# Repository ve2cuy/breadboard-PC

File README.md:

# breadboard-PC — an 8088 computer on a breadboard

A microcomputer with a PC/XT-inspired architecture, built on solderless breadboards around an
**Intel 8088**. Its ROM, whose source code is **written entirely in 8086 assembly language**, boots
into an interactive menu, runs two BASIC interpreters and **boots PC-DOS 2.1, MS-DOS 3.30, 5.0 and
6.22** from 160 KB to 1.44 MB floppy disk images.

A project by Alain Boudreault (VE2CUY), 2026. *[Version française](README_fr.md)*

<p align="center">
  <br>
  <em>The build: the Black Pill STM32F411 bridge (top centre), the 8088, the 8255, the 8259, the ROM and
  the RAM. The LCD shows the “Information” screen (date and time, versions, RAM, disk, speed).</em>
</p>

## At a glance

| | |
|---|---|
| **Processor** | Intel 8088, 4.77 MHz by default, adjustable from 1 to 10 MHz (tested up to 7.38 MHz) |
| **Memory** | 256 KB ROM (W29C020C, `C0000h`–`FFFFFh`); **512 KB** static RAM (AS6C4008, `00000h`–`7FFFFh`), 510 KB of it for DOS |
| **I/O** | 8255A in mode 2 (bus to the bridge), 8259A (interrupts), 4×20 I2C LCD, PS/2 keyboard |
| **Bridge** | WeAct **Black Pill STM32F411** board (firmware 1.6): keyboard, USB terminal, LCD, clock, disk, RESET |
| **Software** | ROM written entirely in assembly (NASM, strict 8086 instruction set): menu, BIOS for DOS, Tiny BASIC, GW-BASIC-style BASIC, RAM test with a memory map |
| **Operating systems** | PC-DOS 2.1, MS-DOS 3.30, 5.0 and 6.22, booted from a floppy disk image (160 KB to 1.44 MB) |

## The build

The core of the machine (processor, address latches, data buffer, ROM, RAM, decoding) is wired on
breadboards with 74LS/74HC logic and no programmable logic (no GAL, no CPLD):

- two **74LS373** latch `A0`–`A7` and `A16`–`A19` on `ALE`; a **74HC245** buffers `D0`–`D7`
  (`DEN`, `DT/R`);
- two **74LS00** do all the decoding, with `M` = memory cycle (`IO/M` = 0):
  - **ROM**: `CE# = NAND(A19, M)` — `C0000h`–`FFFFFh`;
  - **RAM**: `CE# = NAND(/A19, M)` — `00000h`–`7FFFFh`;
  - **8255** (ports `80h`–`83h`): `CS# = NAND(IO, A7)`;
  - **8259** (ports `20h`–`21h`): `CS# = NAND(IO, A5)`;
- the 8088's `RD#` and `WR#` go straight to the ROM, the RAM, the 8255 and the 8259.

<p align="center">
  <br>
  <em>Schematic of the build (KiCad, <a href="kicad/Breadboard-pc">kicad/Breadboard-pc</a>). The clock comes from the
  bridge (<code>CLK_STM</code>) or from an external input, selected by jumper JP1. On the PCB, a third 74LS373 (U12)
  also latches A8-A11, so the whole address bus (A0-A19) can drive two 10-LED bargraphs (readable when single-stepping or halted); J5 brings the bus
  out on a 2 x 20 header.</em>
</p>

<p align="center">
  <br>
  <em>PCB v2 (120 x 124.2 mm, 2 layers), KiCad 3D render: 8088, ZIF socket for the ROM, Black Pill bridge (U5),
  512 KB RAM, 8255, 8259, address bargraphs and J5 bus connector. Routed with Freerouting.</em>
</p>

### The signals in action

The animation follows the machine from RESET to DOS reading a sector: the reset vector fetched from
ROM, a RAM write, programming the 8259 and the interrupt vector table (IVT), a key press and the `IRQ1`
interrupt, a BIOS call (`INT 13h`) and the bridge's burst reply. For each step: the chips involved, the
level of the control signals and the memory area targeted.

The animation is generated by [medias/animation/generer_signaux.py](medias/animation/generer_signaux.py).

## The circuit

The 8088 does not bit-bang any peripheral. All traffic goes through **a single 8255 in mode 2**: an
8-bit bidirectional bus with hardware handshaking, connected to the bridge. Every byte received from
the bridge raises an interrupt (`IR1` of the 8259); during a bridge command, `IR1` is masked and the
BIOS polls for the replies.

```mermaid
flowchart LR
    CPU["Intel 8088"] --- BUS(("Bus<br>A0-A19 / D0-D7"))
    BUS --- ROM["256 KB ROM<br>W29C020C"]
    BUS --- RAM["512 KB RAM<br>AS6C4008"]
    BUS --- PIO["8255A<br>mode 2"]
    BUS --- PIC["8259A"]
    PIO -- "INTR → IR1" --> PIC
    PIC -- INTR --> CPU
    PIO <== "Port A (8 bits) + handshake" ==> BRIDGE["Bridge<br>Black Pill STM32F411"]
    BRIDGE -- "CLK, RESET" --> CPU
    KBD["PS/2 keyboard"] --> BRIDGE
    BRIDGE <-- "USB (serial + drive)" --> PC["PC: terminal"]
    BRIDGE --> LCD["4×20 I2C LCD"]
    BRIDGE --- FLASH["8 MB flash<br>FAT16"]
```

The bridge wiring in detail (pins, 3.3 V / 5 V levels, pull-up resistors) is described (in French) in
[arduino/8088_bridge_stm32/README.md](arduino/8088_bridge_stm32/README.md).

## The STM32 bridge

The bridge firmware (a PlatformIO project, [arduino/8088_bridge_stm32](arduino/8088_bridge_stm32))
gives the 8088 the peripherals of a PC:

| Function | Details |
|---|---|
| **PS/2 keyboard** | Frame decoding; raw scan codes passed to the 8088 |
| **Terminal** | Native USB serial port to the PC (ANSI, 80 columns, UTF-8) |
| **Display** | 4×20 HD44780 LCD over I2C (PCF8574) |
| **Real-time clock** | STM32 RTC (32.768 kHz crystal): `TIME$`, `DATE$`, `INT 1Ah` |
| **Disk** | 8 MB W25Q64 SPI flash formatted FAT16: files, sectors, floppy images mounted as A: (read-only ones too) |
| **Throughput** | Replies sent **in bursts**, as soon as the 8088 has read the previous byte (firmware 1.6) |
| **USB drive** | The flash is exposed to the PC as a USB drive (`USB ON` / `USB OFF`) to copy files onto it |
| **8088 clock** | `CLK` signal generated by hardware PWM, 1 to 10 MHz |
| **8088 RESET** | Held while the bridge starts up; **Ctrl-Alt-Del** (PS/2) or **Ctrl-\\** (terminal) |

The 8088 talks to the bridge through a command protocol on a dedicated channel
(see [Solution-01/lib/bridge.asm](Solution-01/lib/bridge.asm)). The firmware is flashed over USB, with
the board in DFU mode: `platformio run -e blackpill_f411ce_usbdrive -t upload`.

## The menu

At power-up, the ROM displays a menu on both the terminal and the LCD. It can be driven from either
the PS/2 keyboard or the terminal; **Esc** goes back to the previous menu.

| Menu | Options |
|---|---|
| **1) Basic** | Tiny BASIC; GW-BASIC-style BASIC |
| **2) Memory functions** | Memory dump and editing, CPU registers, code entry and execution, interrupt vector table; **RAM test**: *Trace* (full progress), *MAP* (memory map and summary only) or *Loop* (MAP repeated until Esc) |
| **3) USB Disk** | USB drive toggle, file list, **booting a disk image** |
| **4) Configuration** | Clock speed (0.1 and 1 MHz steps; 2.35, 4.77, 8 and 7.2 MHz presets), CPU speed test, date and time, information screen |

The **RAM test** checks all 512 KB byte by byte (the test stack is moved to low RAM, the last 2 KB are
tested separately), then the address lines `A0`–`A18` (the chip's real capacity). It ends with a
**memory map** (one character per KB) and the good and faulty amounts.

## BASIC

An original reimplementation inspired by GW-BASIC: same keywords, same error messages, integers,
single-precision floating point (in software) and strings. About 54 KB are free for programs.

| Category | Commands and functions |
|---|---|
| **Program** | `RUN` `LIST` `EDIT` `DELETE` `NEW` `CLEAR` `CONT` `TRON` `TROFF` `HELP` `SYSTEM` |
| **Control flow** | `IF…THEN…ELSE` `GOTO` `GOSUB`/`RETURN` `ON…GOTO/GOSUB` `FOR…NEXT` `WHILE…WEND` `END` `STOP` |
| **Data** | `LET` `DIM` `ERASE` `SWAP` `DATA`/`READ`/`RESTORE` `DEF FN` `DEFINT`/`DEFSNG`/`DEFSTR` |
| **Input/output** | `PRINT` `INPUT` `LINE INPUT` `INKEY$` `CLS` `LOCATE` `COLOR` `BEEP` |
| **Math** | `ABS` `SGN` `INT` `FIX` `SQR` `SIN` `COS` `TAN` `ATN` `LOG` `EXP` `RND` `RANDOMIZE` |
| **Strings** | `LEN` `LEFT$` `RIGHT$` `MID$` `INSTR` `CHR$` `ASC` `STR$` `VAL` `HEX$` `UCASE$` `STRING$` |
| **Files** | `SAVE` `LOAD` `MERGE` `FILES` `KILL` `FORMAT`; `OPEN` `PRINT #` `INPUT #` `EOF` `CLOSE` |
| **Clock** | `TIMER` `TIME$` `DATE$` (read and set the bridge RTC) |
| **Machine** | `PEEK` `POKE` `DEF SEG` `INP` `OUT` `WAIT` `CALL` `FRE` |
| **Disk and system** | `DSKREAD` `DSKWRITE` `USB ON`/`OFF` `BOOT "image.img"` |

## DOS 2.1 to 6.22

The ROM provides the BIOS layer a DOS expects: disk (`INT 13h`, CHS and LBA), keyboard (`INT 16h`),
clock (`INT 1Ah`), text output to the terminal (`INT 10h`) and bootstrap (`INT 19h`). A floppy image
copied to the flash (through the USB drive) is mounted as drive **A:** and booted from
**USB Disk → 3) Boot disk image**, or with `BOOT "PCDOS2_1.IMG"` from BASIC. DOS writes go to the
image file; a read-only image is mounted anyway, without write access.

<p align="center">
  <br>
  <em>PC-DOS 2.1: booting from the image (one dot per sector read), VER, DIR /W</em>
</p>

<p align="center">
  <br>
  <em>MS-DOS 3.30</em>
</p>

What makes DOS 5.0 and 6.22 possible:

- **512 KB of RAM** (these versions require at least 256 KB);
- the **model byte** `FEh` (PC/XT) at `F000:FFFE`: without it, DOS 5 takes the AT keyboard path
  (ports `60h`/`64h`), which hits the 8259 with this decoding;
- the BIOS tick counter `0040:006C`, kept in step with the bridge clock (there is no timer on this
  build): DOS 6 times its F5/F8 boot pause with it;
- **1.44 MB** floppies (geometry from the image size, `INT 13h AH=08h/18h`).

DOS accented letters and box-drawing characters (code page 437) are converted to **UTF-8** on the
terminal: the PC terminal must be set to UTF-8.

Limitations: no video hardware (programs that write to video memory display nothing); DOS keyboard
input from the terminal only; **KEYB** does not work (it reads the keyboard through port `60h`) —
setup disks that start it from `AUTOEXEC.BAT` must have it removed (see the `-nokeyb` copies in
[PC-DOS/](PC-DOS)).

## Building the ROM

```sh
cd Solution-01
make            # solution-01.bin (256 KB, 512 KB RAM); make rom-en for English; make rom-128: 128 KB RAM
make check      # checks size, reset vector, signature and model byte
make test       # test benches under emulation (Unicorn)
make test-rom   # full ROM simulation: DOS, BASIC, PS/2 keyboard
```

Tools: NASM, GNU Make, Python 3 (+ `unicorn` for the tests); PlatformIO for the bridge.

## Repository layout

| Folder | Contents |
|---|---|
| [Solution-01/](Solution-01) | 8088 ROM (NASM) and tests; full technical documentation (in French) in [Solution-01/README.md](Solution-01/README.md) |
| [arduino/8088_bridge_stm32/](arduino/8088_bridge_stm32) | Firmware of the Black Pill STM32F411 bridge (PlatformIO) |
| [kicad/](kicad) | Schematic and PCB of the build |
| [PC-DOS/](PC-DOS) | Test floppy disk images |
| [medias/](medias) | Datasheets, schematic, PCB render, signal animation and screenshots |

> The terminal screenshots on this page are produced by the actual (English) ROM, running in the
> project's simulator ([medias/captures/generer.py](medias/captures/generer.py)).

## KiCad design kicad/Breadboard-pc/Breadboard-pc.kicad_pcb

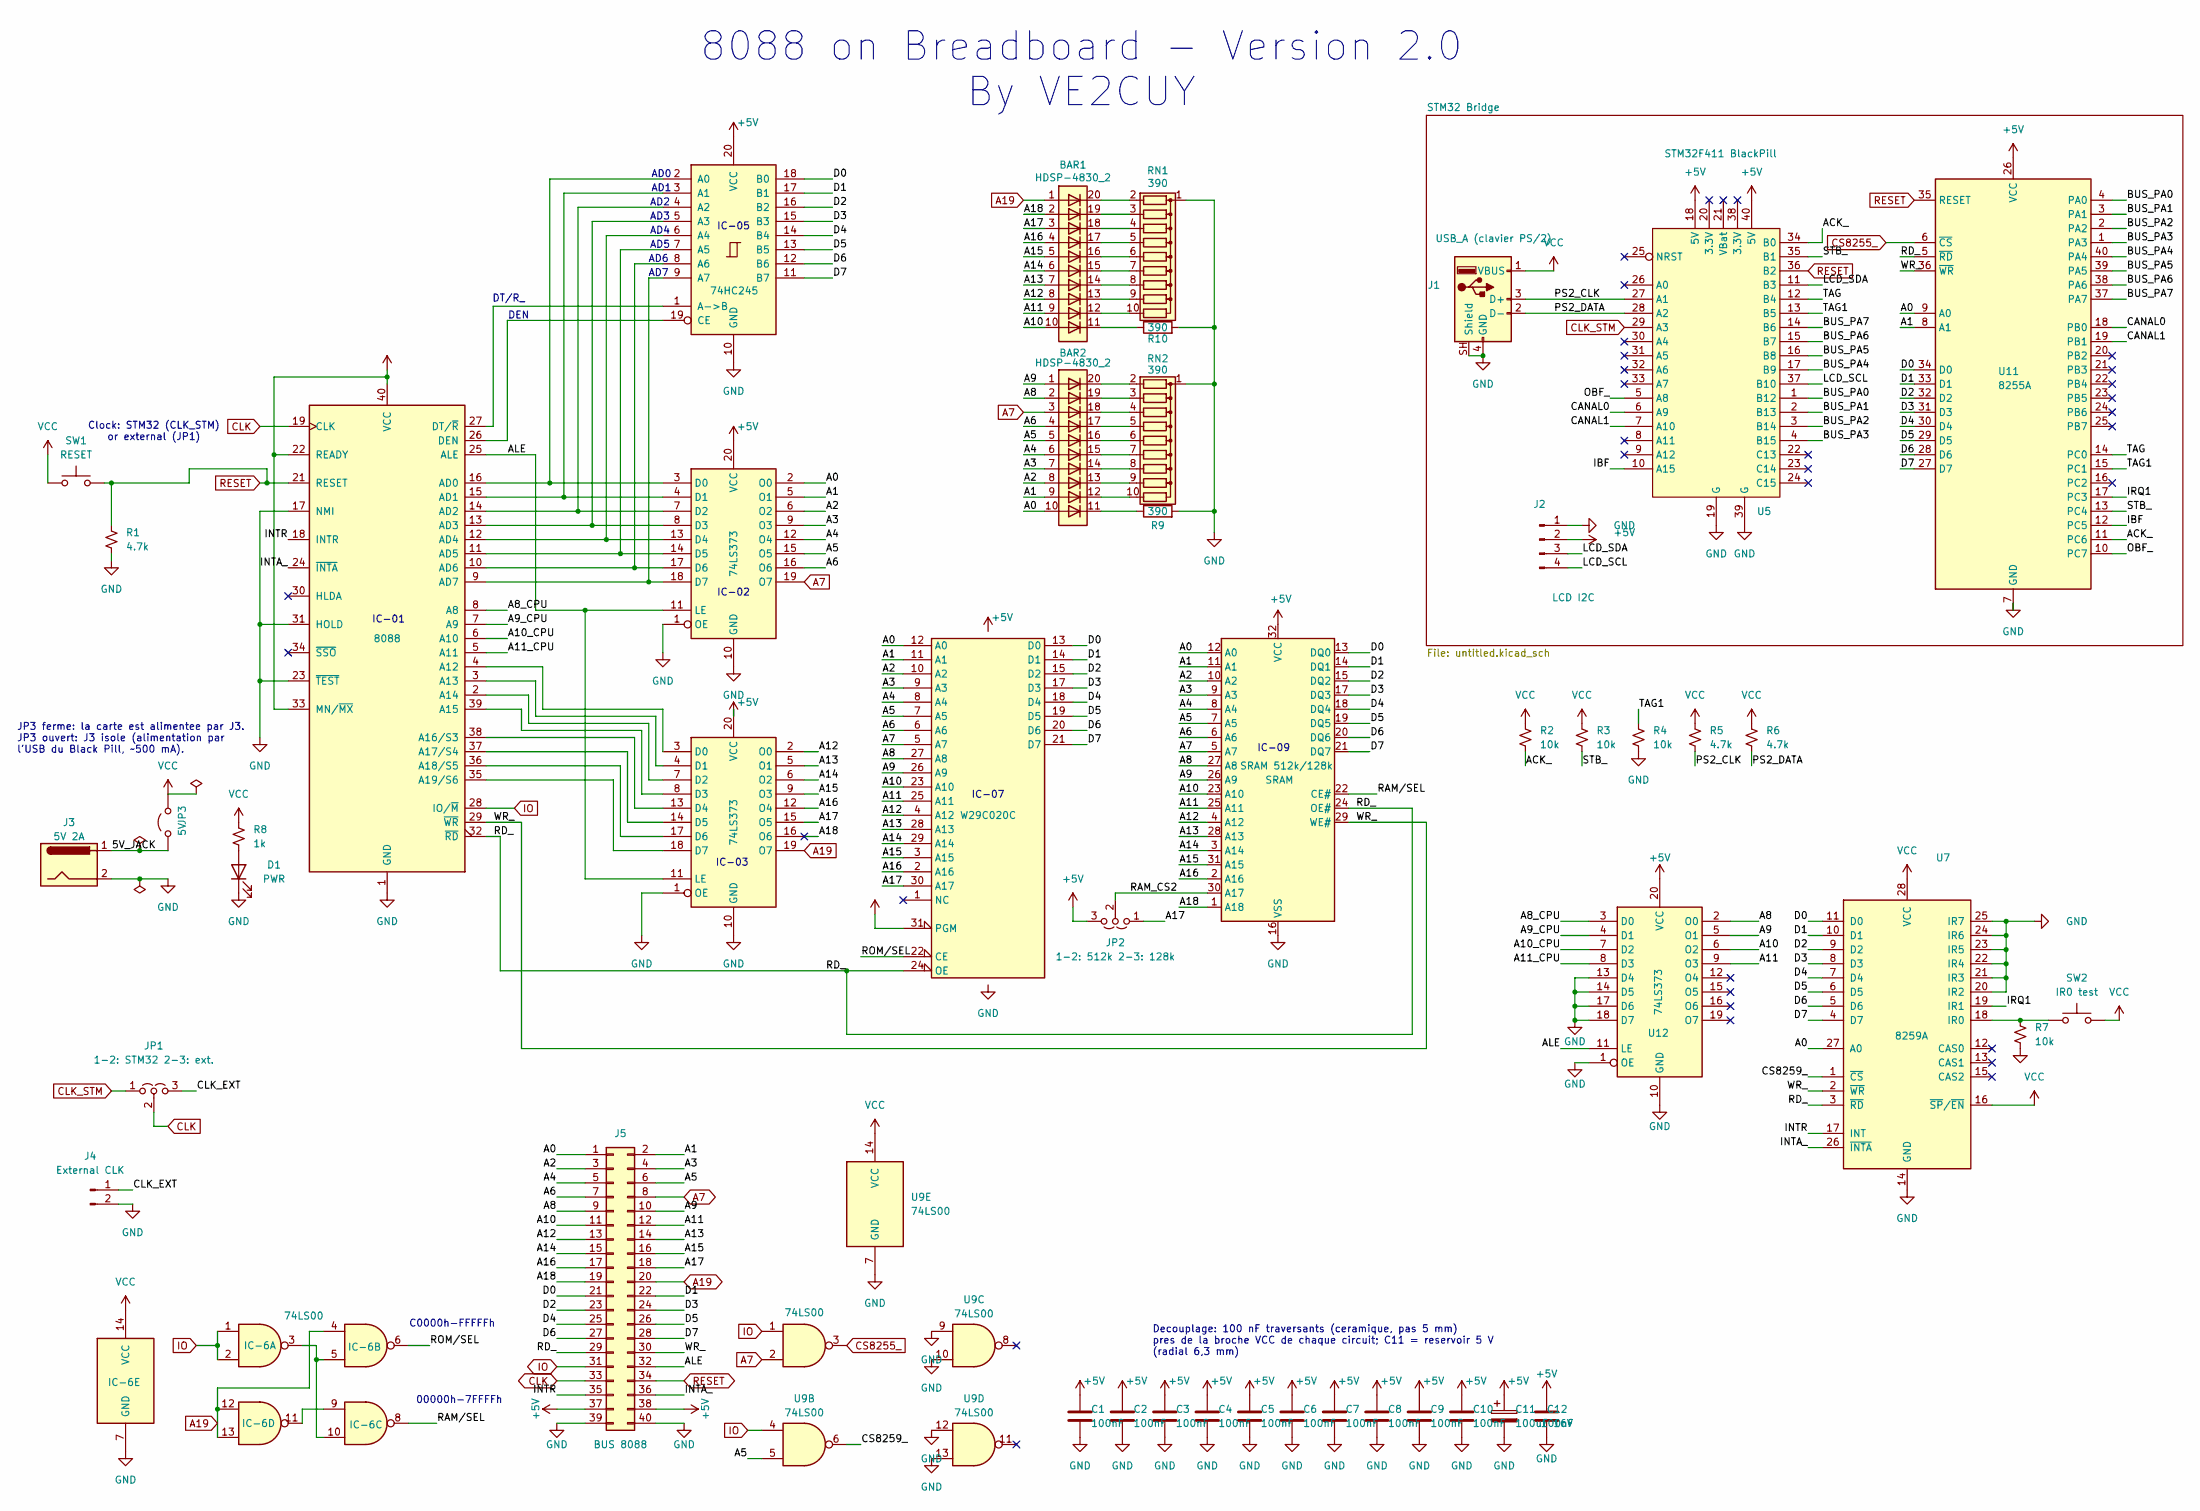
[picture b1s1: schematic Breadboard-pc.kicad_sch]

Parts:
BAR1, BAR2: HDSP-4830_2; HDSP-4830
C1, C2, C3, C4, C5, C6, C7, C8, C9, C10, C12: 100nF; C_Disc_D5.0mm_W2.5mm_P5.00mm
C11: 100uF 16V; CP_Radial_D6.3mm_P2.50mm
D1: PWR; LED_D3.0mm
IC-6: 74LS00; DIP-14_W7.62mm
J1: USB_A (clavier PS/2); USB_A_Molex_67643_Horizontal
J2: LCD I2C; PinHeader_1x04_P2.54mm_Vertical
J3: 5V 2A; BarrelJack_Horizontal
J4: External CLK; PinHeader_1x02_P2.54mm_Vertical
J5: BUS 8088; PinHeader_2x20_P2.54mm_Vertical
JP1: 1-2: STM32 2-3: ext.; PinHeader_1x03_P2.54mm_Vertical
JP2: 1-2: 512k 2-3: 128k; PinHeader_1x03_P2.54mm_Vertical
JP3: 5V; PinHeader_1x02_P2.54mm_Vertical
R1, R5, R6: 4.7k; R_Axial_DIN0207_L6.3mm_D2.5mm_P7.62mm_Horizontal
R2, R3, R4, R7: 10k; R_Axial_DIN0207_L6.3mm_D2.5mm_P7.62mm_Horizontal
R8: 1k; R_Axial_DIN0207_L6.3mm_D2.5mm_P7.62mm_Horizontal
R9, R10: 390; R_Axial_DIN0207_L6.3mm_D2.5mm_P7.62mm_Horizontal
RN1, RN2: 390; R_Array_SIP10
SW1: RESET; SW_PUSH_6mm
SW2: IR0 test; SW_PUSH_6mm
U1: 8088; DIP-40_W15.24mm
U2, U3, U12: 74LS373; DIP-20_W7.62mm
U4: W29C020C; DIP_Socket-32_W11.9mm_W12.7mm_W15.24mm_W17.78mm_W18.5mm_3M_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
U5: STM32F411 BlackPill; STM32F411_Black_Pill
U6: 74HC245; DIP-20_W7.62mm
U7: 8259A; DIP-28_W15.24mm
U8: SRAM; DIP-32_W15.24mm
U9: 74LS00; DIP-14_W7.62mm
U11: 8255A; DIP-40_W15.24mm

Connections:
/5V_JACK: J3.1, JP3.1 (A)
/A0: BAR2.10 (A), J5.1, U2.2 (O0), U4.12 (A0), U7.27 (A0), U8.12 (A0), U11.9 (A0)
/A1: BAR2.9 (A), J5.2, U2.5 (O1), U4.11 (A1), U8.11 (A1), U11.8 (A1)
/A2: BAR2.8 (A), J5.3, U2.6 (O2), U4.10 (A2), U8.10 (A2)
/A3: BAR2.7 (A), J5.4, U2.9 (O3), U4.9 (A3), U8.9 (A3)
/A4: BAR2.6 (A), J5.5, U2.12 (O4), U4.8 (A4), U8.8 (A4)
/A5: BAR2.5 (A), J5.6, U2.15 (O5), U4.7 (A5), U8.7 (A5), U9.5
/A6: BAR2.4 (A), J5.7, U2.16 (O6), U4.6 (A6), U8.6 (A6)
/A8: BAR2.2 (A), J5.9, U4.27 (A8), U8.27 (A8), U12.2 (O0)
/A8_CPU: U1.8 (A8), U12.3 (D0)
/A9: BAR2.1 (A), J5.10, U4.26 (A9), U8.26 (A9), U12.5 (O1)
/A9_CPU: U1.7 (A9), U12.4 (D1)
/A10: BAR1.10 (A), J5.11, U4.23 (A10), U8.23 (A10), U12.6 (O2)
/A10_CPU: U1.6 (A10), U12.7 (D2)
/A11: BAR1.9 (A), J5.12, U4.25 (A11), U8.25 (A11), U12.9 (O3)
/A11_CPU: U1.5 (A11), U12.8 (D3)
/A12: BAR1.8 (A), J5.13, U3.2 (O0), U4.4 (A12), U8.4 (A12)
/A13: BAR1.7 (A), J5.14, U3.5 (O1), U4.28 (A13), U8.28 (A13)
/A14: BAR1.6 (A), J5.15, U3.6 (O2), U4.29 (A14), U8.3 (A14)
/A15: BAR1.5 (A), J5.16, U3.9 (O3), U4.3 (A15), U8.31 (A15)
/A16: BAR1.4 (A), J5.17, U3.12 (O4), U4.2 (A16), U8.2 (A16)
/A17: BAR1.3 (A), J5.18, JP2.1 (A), U3.15 (O5), U4.30 (A17)
/A18: BAR1.2 (A), J5.19, U3.16 (O6), U8.1 (NC)
/ACK_: R2.2, U5.34 (B0), U11.11 (PC6)
/ALE: J5.32, U1.25 (ALE), U2.11 (LE), U3.11 (LE), U12.11 (LE)
/BUS_PA0: U5.1 (B12), U11.4 (PA0)
/BUS_PA1: U5.2 (B13), U11.3 (PA1)
/BUS_PA2: U5.3 (B14), U11.2 (PA2)
/BUS_PA3: U5.4 (B15), U11.1 (PA3)
/BUS_PA4: U5.17 (B9), U11.40 (PA4)
/BUS_PA5: U5.16 (B8), U11.39 (PA5)
/BUS_PA6: U5.15 (B7), U11.38 (PA6)
/BUS_PA7: U5.14 (B6), U11.37 (PA7)
/CANAL0: U5.6 (A9), U11.18 (PB0)
/CANAL1: U5.7 (A10), U11.19 (PB1)
/CLK_EXT: J4.1, JP1.3 (B)
/CS8259_: U7.1 (~CS), U9.6
/D0: J5.21, U4.13 (D0), U6.18 (B0), U7.11 (D0), U8.13 (DQ0), U11.34 (D0)
/D1: J5.22, U4.14 (D1), U6.17 (B1), U7.10 (D1), U8.14 (DQ1), U11.33 (D1)
/D2: J5.23, U4.15 (D2), U6.16 (B2), U7.9 (D2), U8.15 (DQ2), U11.32 (D2)
/D3: J5.24, U4.17 (D3), U6.15 (B3), U7.8 (D3), U8.17 (DQ3), U11.31 (D3)
/D4: J5.25, U4.18 (D4), U6.14 (B4), U7.7 (D4), U8.18 (DQ4), U11.30 (D4)
/D5: J5.26, U4.19 (D5), U6.13 (B5), U7.6 (D5), U8.19 (DQ5), U11.29 (D5)
/D6: J5.27, U4.20 (D6), U6.12 (B6), U7.5 (D6), U8.20 (DQ6), U11.28 (D6)
/D7: J5.28, U4.21 (D7), U6.11 (B7), U7.4 (D7), U8.21 (DQ7), U11.27 (D7)
/IBF: U5.10 (A15), U11.12 (PC5)
/INTA_: J5.36, U1.24 (~INTA), U7.26 (~INTA)
/INTR: J5.35, U1.18 (INTR), U7.17 (INT)
/IRQ1: U7.19 (IR1), U11.17 (PC3)
/LCD_SCL: J2.4, U5.37 (B10)
/LCD_SDA: J2.3, U5.11 (B3)
/OBF_: U5.5 (A8), U11.10 (PC7)
/PS2_CLK: J1.3 (D+), R5.2, U5.27 (A1)
/PS2_DATA: J1.2 (D-), R6.2, U5.28 (A2)
/RAM_CS2: JP2.2 (C), U8.30 (CS2)
/RAM/SEL: IC-6.8, U8.22 (CE#)
/RD_: J5.29, U1.32 (~RD), U4.24 (OE), U7.3 (~RD), U8.24 (OE#), U11.5 (~RD)
/ROM/SEL: IC-6.6, U4.22 (CE)
/STB_: R3.2, U5.35 (B1), U11.13 (PC4)
/TAG: U5.12 (B4), U11.14 (PC0)
/TAG1: R4.1, U5.13 (B5), U11.15 (PC1)
/WR_: J5.30, U1.29 (~WR), U7.2 (~WR), U8.29 (WE#), U11.36 (~WR)
A7: BAR2.3 (A), J5.8, U2.19 (O7), U4.5 (A7), U8.5 (A7), U9.2
A19: BAR1.1 (A), IC-6.4, IC-6.12, IC-6.13, J5.20, U3.19 (O7)
CLK: J5.33, JP1.2 (C), U1.19 (CLK)
CLK_STM: JP1.1 (A), U5.29 (A3)
CS8255_: U9.3, U11.6 (~CS)
GND: C1.2, C2.2, C3.2, C4.2, C5.2, C6.2, C7.2, C8.2, C9.2, C10.2, C11.2, C12.2, D1.1 (K), IC-6.7 (GND), J1.4 (GND), J1.SH (Shield), J2.1, J3.2, J4.2, J5.39, J5.40, R1.2, R4.2, R7.2, R9.2, R10.2, RN1.1 (common), RN2.1 (common), U1.1 (GND), U1.17 (NMI), U1.20 (GND), U1.23 (~TEST), U1.31 (HOLD), U2.1 (OE), U2.10 (GND), U3.1 (OE), U3.10 (GND), U4.16 (GND), U5.19 (G), U5.39 (G), U6.10 (GND), U7.14 (GND), U7.20 (IR2), U7.21 (IR3), U7.22 (IR4), U7.23 (IR5), U7.24 (IR6), U7.25 (IR7), U8.16 (VSS), U9.7 (GND), U9.9, U9.10, U9.12, U9.13, U11.7 (GND), U12.1 (OE), U12.10 (GND), U12.13 (D4), U12.14 (D5), U12.17 (D6), U12.18 (D7)
IO: IC-6.1, IC-6.2, J5.31, U1.28 (IO/~M), U9.1, U9.4
unnamed: BAR1.11 (K), R10.1
unnamed: BAR2.11 (K), R9.1
unnamed: D1.2 (A), R8.2
unnamed: IC-6.3, IC-6.5, IC-6.10
unnamed: IC-6.9, IC-6.11
unnamed: BAR1.20 (K), RN1.2 (R1)
unnamed: BAR1.19 (K), RN1.3 (R2)
unnamed: BAR1.18 (K), RN1.4 (R3)
unnamed: BAR1.17 (K), RN1.5 (R4)
unnamed: BAR1.16 (K), RN1.6 (R5)
unnamed: BAR1.15 (K), RN1.7 (R6)
unnamed: BAR1.14 (K), RN1.8 (R7)
unnamed: BAR1.13 (K), RN1.9 (R8)
unnamed: BAR1.12 (K), RN1.10 (R9)
unnamed: BAR2.20 (K), RN2.2 (R1)
unnamed: BAR2.19 (K), RN2.3 (R2)
unnamed: BAR2.18 (K), RN2.4 (R3)
unnamed: BAR2.17 (K), RN2.5 (R4)
unnamed: BAR2.16 (K), RN2.6 (R5)
unnamed: BAR2.15 (K), RN2.7 (R6)
unnamed: BAR2.14 (K), RN2.8 (R7)
unnamed: BAR2.13 (K), RN2.9 (R8)
unnamed: BAR2.12 (K), RN2.10 (R9)
unnamed: U1.4 (A12), U3.3 (D0)
unnamed: U1.3 (A13), U3.4 (D1)
unnamed: U1.2 (A14), U3.7 (D2)
unnamed: U1.39 (A15), U3.8 (D3)
unnamed: U1.38 (A16/S3), U3.13 (D4)
unnamed: U1.37 (A17/S4), U3.14 (D5)
unnamed: U1.36 (A18/S5), U3.17 (D6)
unnamed: U1.35 (A19/S6), U3.18 (D7)
unnamed: U1.16 (AD0), U2.3 (D0), U6.2 (A0)
unnamed: U1.15 (AD1), U2.4 (D1), U6.3 (A1)
unnamed: U1.14 (AD2), U2.7 (D2), U6.4 (A2)
unnamed: U1.13 (AD3), U2.8 (D3), U6.5 (A3)
unnamed: U1.12 (AD4), U2.13 (D4), U6.6 (A4)
unnamed: U1.11 (AD5), U2.14 (D5), U6.7 (A5)
unnamed: U1.10 (AD6), U2.17 (D6), U6.8 (A6)
unnamed: U1.9 (AD7), U2.18 (D7), U6.9 (A7)
unnamed: U1.26 (DEN), U6.19 (CE)
unnamed: U1.27 (DT/~R), U6.1 (A->B)
unnamed: R7.1, SW2.1, U7.18 (IR0)
RESET: J5.34, R1.1, SW1.2, U1.21 (RESET), U5.36 (B2), U11.35 (RESET)

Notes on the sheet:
IC-07
Decouplage: 100 nF traversants (ceramique, pas 5 mm) pres de la broche VCC de chaque circuit; C11 = reservoir 5 V (radial 6,3 mm)
C0000h-FFFFFh
00000h-7FFFFh
IC-05
AD2
DEN
IC-01
AD5
IC-03
AD4
AD0
DT/R_
IC-09
AD3
JP3 ferme: la carte est alimentee par J3. JP3 ouvert: J3 isole (alimentation par l'USB du Black Pill, ~500 mA).
IC-02
AD6
AD1
Clock: STM32 (CLK_STM) or external (JP1)
AD7
8088 on Breadboard - Version 2.0 By VE2CUY

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
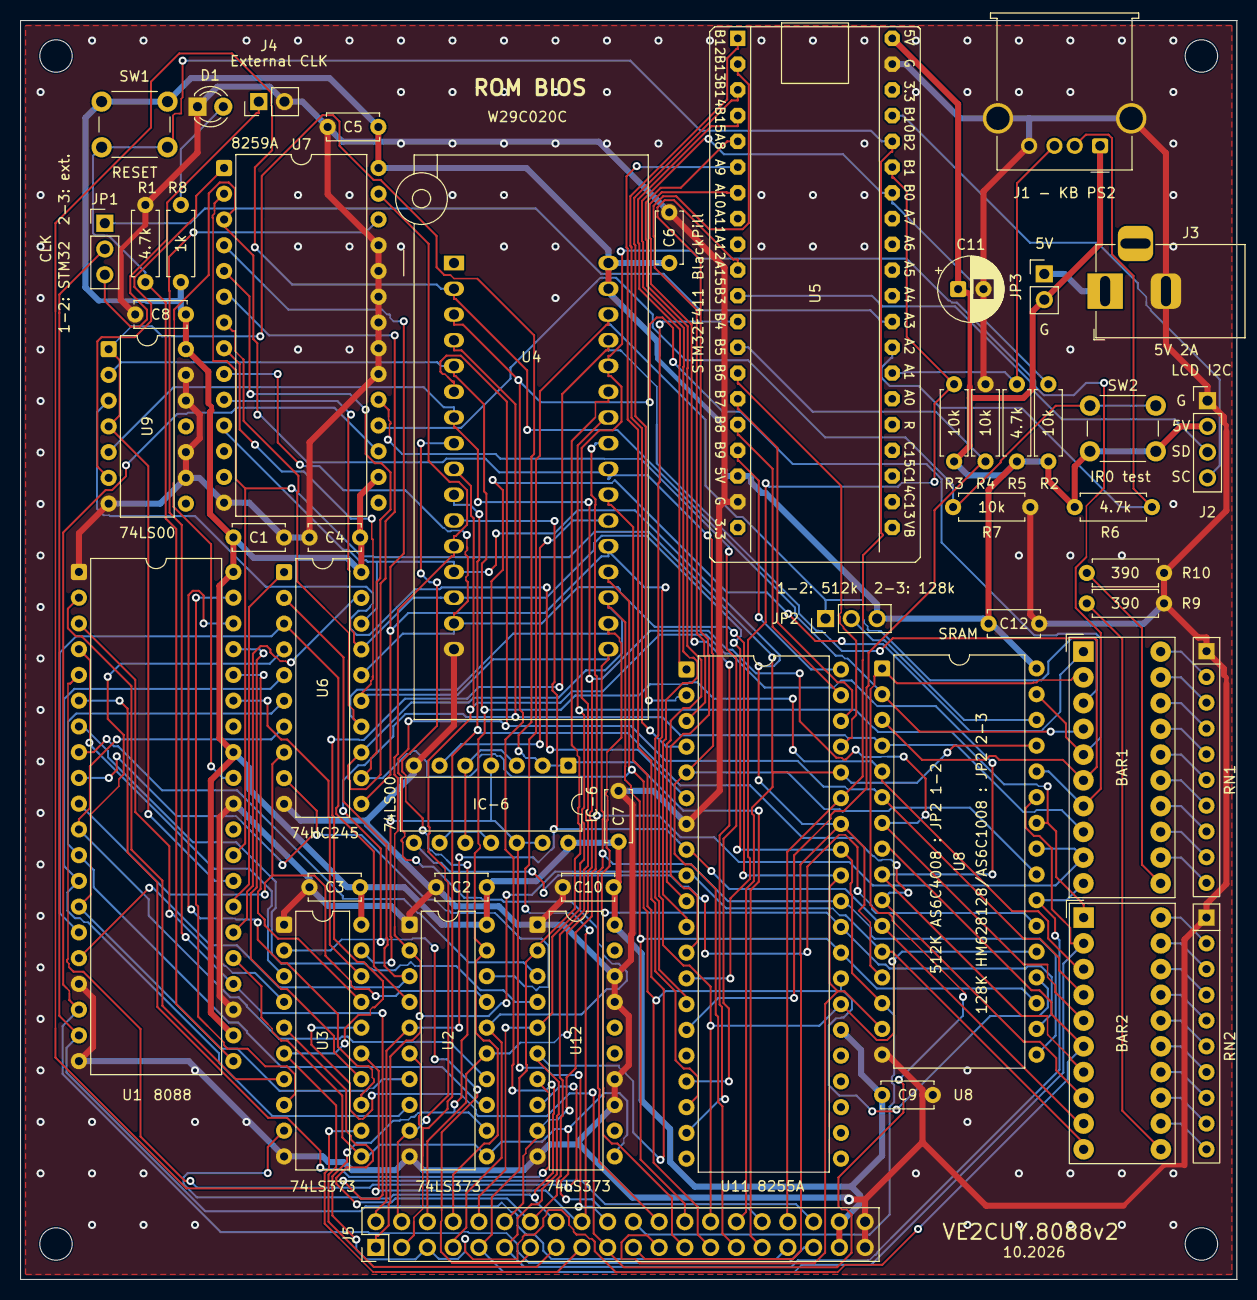
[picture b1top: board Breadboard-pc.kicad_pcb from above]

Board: 2 copper layers, 120.0 x 124.2 mm, 53 parts (0 on the bottom side), 113 nets.

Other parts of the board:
H1, H2, H3, H4: M3; MountingHole_3.2mm_M3

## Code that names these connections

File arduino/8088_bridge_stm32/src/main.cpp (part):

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//   - UART          : port serie virtuel USB (USB natif, "Serial") <-> 8088;
//   - LCD 20x4 I2C  : possede le bus I2C et le protocole PCF8574/HD44780.
//
// 8088 -> pont : le 8088 pose le CANAL sur le Port B (PB0/PB1 du 8255) puis
//     ecrit le Port A; OBF# passe a 0. On lit le canal, on abaisse ACK#, on lit
//     l'octet, on relache ACK#. canal 0 = octet UART, 1 = commande LCD, 2 =
//     donnee LCD.
// pont -> 8088 : on pose l'etiquette TAG (PC0: 0 = scan code, 1 = octet UART
//     recu; PC1 = 1: REPONSE a une commande), l'octet sur le bus, et on pulse
//     STB#; INTR du 8255 (sur IR1 du 8259) interrompt le 8088.
// canal 3 = COMMANDES pour le pont (voir Solution-01/lib/bridge.asm):
//     00h PING (reponse B1h, 3, capacites)   01h LIRE l'heure (reponse: 8 octets)
//     02h + 7 octets REGLER l'heure (annee 2 octets, mois, jour, h, min, s).
//     03h VERSION du firmware (PAS le "3" de PING ci-dessus, qui est le numero
//     de VERSION DU PROTOCOLE - sans rapport) -> 2 octets (majeure, mineure).
//     Necessite TAG1 (PB5) relie a PC1 du 8255 (tire a 0 par 10 kohm).
//     10h-19h = DISQUE: fichiers FAT (racine, noms 8.3) sur la flash SPI (W25Q64, 8 Mo) de la carte
//     (PA4 = CS, SPI1 PA5/PA6/PA7): statut, formater, ouvrir, lire, ecrire, fermer,
//     repertoire (debut / suivant), supprimer, espace libre. Voir lib/bridge.asm.
//     2Ch + 1 octet (action) = HORLOGE du 8088 (PA3, PWM materiel, voir clockExec ci-dessous):
//     0 lire, 1 +0,1 MHz, 2 -0,1 MHz, 3 +1 MHz, 4 -1 MHz, 5 -> 4,77 MHz, 6 -> 8 MHz
//     -> reponse 4 octets = Hz resultant.
//
// CABLAGE (voir le tableau du README.md)
//   D0-D3 <-> PB12-PB15 et D4-D7 <-> PB6-PB9  <->  8255 PA0-PA7 (bus de donnees)
//   PB0 -> ACK# (PC6)   PB1 -> STB# (PC4)   PA8 <- OBF# (PC7)   PB4 -> TAG (PC0)
//   PA9 <- canal bit 0 (8255 PB0)   PA10 <- canal bit 1 (8255 PB1)
//   PA15 <- IBF (PC5, facultatif)   PB5 -> TAG1 (PC1)
//   PA3 -> CLK du 8088 (broche 19, PWM materiel TIM2 CH4 - remplace le fil depuis l'Arduino UNO
//   R4 de projets/Clock-8088/; PA3 servait a TAG2/PC2, jamais cablee sur ce montage - libre)
//   PA1 <- CLK PS/2   PA2 <- DATA PS/2   PB10 = SCL, PB3 = SDA (LCD I2C2)
//   PA11/PA12 = USB, PA13/PA14 = SWD, PC13 = LED, PA4-PA7 = flash SPI (reservees),
//   PB2 -> RESET du 8088 (broche 21, actif HAUT; 4,7 kohm (R1) vers la masse sur le montage, bouton vers +5 V):
//   poussee HAUT pour un reset (demarrage du pont, Ctrl-Alt-Suppr au PS/2, Ctrl-\ au terminal), sinon
//   ENTREE (ne gene pas le bouton, jamais forcee BAS). PB2 = BOOT1: au repos la ligne est BASSE (4,7 kohm),
//   le mode DFU (BOOT0 = 1, BOOT1 = 0) reste donc utilisable.   PA0 = bouton K1 de la carte
// Selon la fiche technique du STM32F411 (DS10314 Rev 8, tableau 8), TOUTES ces
// broches sont tolerantes 5 V (FT) SAUF PA0 et PB5 (TC, 3,3 V): PB5 n'est donc
// utilisee qu'en SORTIE (TAG1). Ne jamais y relier une sortie 5 V.
// ============================================================================
#include <Wire.h>
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
// ---- reglages -------------------------------------------------------------
#define LCD_ADDR    0x27     // 0x3F pour un PCF8574A
// IBF (PC5 du 8255) cable sur PA15 ? 1 = oui: on n'envoie un octet que si le 8088 a lu le
// precedent (aucun octet ecrase); 0 = non cable. Non cable, PA15 est tiree a 0 (= libre).
#define USE_IBF     1
// Espace MINIMAL entre deux octets pont -> 8088, en plus de IBF. Le 8088 met ~ 0,5 ms
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#define IBF_BIT   15                 // GPIOA, entree (facultatif)
#define PS2_CLK_BIT  1               // GPIOA, interruption EXTI1
#define PS2_DATA_BIT 2               // GPIOA
const uint32_t PIN_ACK = PB0, PIN_STB = PB1, PIN_TAG = PB4;
const uint32_t PIN_OBF = PA8, PIN_CH0 = PA9, PIN_CH1 = PA10, PIN_IBF = PA15;
const uint32_t PIN_TAG1 = PB5;                         // PC1 (etiquette etendue, futur)
const uint32_t PIN_PS2_CLK = PA1, PIN_PS2_DATA = PA2;
const uint32_t PIN_SCL = PB10, PIN_SDA = PB3;          // I2C2 (AF4 / AF9)
const uint32_t PIN_CLK8088 = PA3;                      // TIM2 CH4: horloge du 8088 (broche CLK, 19) -
                                                         // remplace le fil depuis l'Arduino UNO R4 (projets/Clock-8088)
                                                         // - PA3 servait a TAG2/PC2, jamais cablee sur ce montage

// Bus de donnees sur GPIOB, en deux quartets: D0-D3 = PB12-PB15, D4-D7 = PB6-PB9
#define BUS_ODR_MASK   ((0xFUL << 12) | (0xFUL << 6))
#define BUS_MODER_MASK 0xFF0FF000UL  // 2 bits par broche: PB12-15 (bits 24-31) et PB6-9 (bits 12-19)
#define BUS_MODER_OUT  0x55055000UL  // 01 = sortie
// Sur le montage, les broches PA4-PA7 du 8255 arrivent dans l'ORDRE INVERSE
// (constate: espace 0x20 recu 0x40, 'p' 0x70 recu 0xE0): le quartet haut est
// inverse (D4<->D7, D5<->D6), comme sur l'UNO. 1 = corrige en logiciel, 0 = bus
// cable dans l'ordre (D0-D7 <-> PA0-PA7).
#define BUS_HIGH_NIBBLE_REVERSED 1

// ---- canaux 8088 -> pont (Port B du 8255) ---------------------------------
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  stbHigh();                               // front montant: le 8255 verrouille
  delayMicroseconds(2);
#if DEBUG_FS
  dbgIbfAfter = (uint8_t)((GPIOA->IDR >> IBF_BIT) & 1);   // IBF doit valoir 1 (octet non lu)
#endif
  busRelease();
}
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}

// ============================================================================
// Horloge du 8088 (PA3 = TIM2 CH4, PWM materiel, duty cycle fixe 1/3 - voir
// projets/Clock-8088/src/main.cpp, meme principe mais sur l'Arduino UNO R4 separe
// d'origine: ici, l'horloge est generee par CE MEME pont, plus besoin de 2e carte).
// clockSetup() DOIT etre appelee EN PREMIER dans setup() (avant SPI/USB/RTC, qui
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
// ============================================================================
// Disque: systeme de fichiers FAT sur la flash SPI (W25Q64, 8 Mo) de la carte.
// Le STM32F411 n'a pas de QUADSPI: la flash s'utilise en SPI simple (SPI1: PA4 = CS,
// PA5 = SCK, PA6 = MISO, PA7 = MOSI). Fichiers a la racine, noms 8.3.
// ============================================================================
static Adafruit_FlashTransport_SPI flashTransport(PA4, SPI);
static Adafruit_SPIFlash flash(&flashTransport);
static FatVolume fatfs;
static bool flashOk = false, fsOk = false;
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#define RESET8088_BIT      2               // GPIOB
#define RESET8088_PULSE_MS 10UL            // >> 4 cycles d'horloge exiges par le 8088
#define RESET_UART_KEY     0x1C            // Ctrl-\ (terminal)
#define STUCK_MS           500UL           // IBF = 1 depuis ce delai: le 8088 ne lit plus (fige)
static volatile bool resetRequest = false;

static void reset8088Hold() {              // sortie HAUTE (ODR avant MODER: aucune impulsion basse)
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  // ACK#/STB#: DRAIN OUVERT. Le niveau haut est fourni par les 10 kohm vers +5 V
  // (vrai niveau 5 V pour le 8255, et lignes tenues hautes pendant un reset du
  // STM32). Pull-up interne en secours (3,3 V, suffisant pour l'entree TTL du 8255).
  pinMode(PIN_ACK, OUTPUT_OPEN_DRAIN);  ackHigh();  pullUp(GPIOB, ACK_BIT);
  pinMode(PIN_STB, OUTPUT_OPEN_DRAIN);  stbHigh();  pullUp(GPIOB, STB_BIT);
  pinMode(PIN_TAG, OUTPUT);   digitalWrite(PIN_TAG, LOW);
  pinMode(PIN_TAG1, OUTPUT);  digitalWrite(PIN_TAG1, LOW);   // PC1 (inutilise pour l'instant)
  pinMode(PIN_OBF, INPUT_PULLUP);          // 8255 absent/hors tension = "rien"
  pinMode(PIN_CH0, INPUT);
  pinMode(PIN_CH1, INPUT);
  pinMode(PIN_IBF, INPUT_PULLDOWN);        // non cable = "libre"

  // Bus (PB6-PB9, PB12-PB15): entrees, sans pull, sorties push-pull rapides.
  // (L'horloge de GPIOB est deja activee par les pinMode() ci-dessus.)
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  Wire.setClock(100000);
  lcdInit();

  pinMode(PIN_PS2_CLK, INPUT_PULLUP);      // + pull-ups externes 4,7-10 kohm vers +5 V conseilles
  pinMode(PIN_PS2_DATA, INPUT_PULLUP);
  attachInterrupt(digitalPinToInterrupt(PIN_PS2_CLK), ps2Isr, FALLING);

  delay(RESET8088_PULSE_MS);               // pont pret: le 8088 demarre (horloge stable depuis clockSetup)
  reset8088Release();
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static uint32_t lastTx = 0;                // date du dernier octet envoye (USE_IBF=0)
static bool canSend() {
#if USE_IBF
  if ((GPIOA->IDR >> IBF_BIT) & 1) return false;   // IBF = 1: le 8088 n'a pas encore lu l'octet precedent
#endif
  return (uint32_t)(micros() - lastTx) >= GAP_US;
}
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    else if (since == 0) since = millis() | 1;
    else if (!said && millis() - since > 100) {
      said = true;
      UsbSerial.print("[rq] bloquee: IBF="); UsbSerial.print((GPIOA->IDR >> IBF_BIT) & 1);
      UsbSerial.print(" ps2Quiet="); UsbSerial.print(ps2Quiet(BUS_QUIET_US));
      UsbSerial.print(" n="); UsbSerial.print((uint8_t)((rqHead - rqTail) & 63)); UsbSerial.print("\r\n");
    }
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
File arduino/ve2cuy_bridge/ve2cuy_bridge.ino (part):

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// Le 8088 ne voit qu'UN bus de 8 bits: le Port A du 8255 en MODE 2, avec la
// poignee de main materielle du 8255 (voir Directives.md, hardware.inc):
//
//   8088 -> Arduino : le 8088 pose le CANAL sur le Port B (PB0/PB1) puis ecrit
//       le Port A; OBF# (PC7) passe a 0. On lit le canal, on abaisse ACK#
//       (PC6): le 8255 pilote alors le bus, on lit l'octet, on relache ACK#.
//       canal 0 = octet UART a emettre, 1 = commande LCD, 2 = donnee LCD.
//   Arduino -> 8088 : on pose l'etiquette (PC0: 0 = scan code, 1 = octet UART
//       recu), on pose l'octet sur le bus et on pulse STB# (PC4); INTR du 8255
//       (cable sur IR1 du 8259) interrompt le 8088.
//
// CABLAGE (18 broches, aucun circuit integre supplementaire)
//   D2  <- CLK  clavier PS/2 (interruption INT0)
//   D3  <- DATA clavier PS/2
//   D4  -> ACK#  8255 PC6        (repos: HAUT)   + pull-up 10k vers +5V conseille
//   D5  -> STB#  8255 PC4        (repos: HAUT)   + pull-up 10k vers +5V conseille
//   D6  <- OBF#  8255 PC7
//   D7  -> TAG   8255 PC0
//   D8  <- CH0   8255 PB0
//   D9  <- CH1   8255 PB1
//   D10 D11 D12 D13 A3 A2 A1 A0  <->  8255 PA0 PA1 PA2 PA3 PA4 PA5 PA6 PA7
//   (soit D10-D13 = PA0-PA3, A3=PA4, A2=PA5, A1=PA6, A0=PA7 - voir BUS[])
//   A4 (SDA), A5 (SCL) -> module LCD I2C (PCF8574, adresse 0x27 ou 0x3F)
//   INTR du 8255 (PC3) -> IR1 du 8259 (plus aucune sortie IR sur l'Arduino)
//   D0/D1 : reserves a l'USB (UART vers le PC) - ne rien y brancher.
//   Masse commune Arduino / breadboard 8088.
//
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#define DEBUG_PS2   0        // 1 = trace PS/2 sur le terminal (Serial), voir dbg*()

// ---- broches --------------------------------------------------------------
const uint8_t PIN_PS2_CLK  = 2;   // = PD2 (INT0) - ps2Isr lit PIND directement: garder CLK/DATA sur PD0-PD7
const uint8_t PIN_PS2_DATA = 3;
const uint8_t PIN_ACK      = 4;
const uint8_t PIN_STB      = 5;
const uint8_t PIN_OBF      = 6;
const uint8_t PIN_TAG      = 7;
const uint8_t PIN_CH0      = 8;
const uint8_t PIN_CH1      = 9;
// Ordre selon le CABLAGE REEL constate sur le montage: A0..A3 sont relies a
// PA7..PA4 (ordre inverse - les broches du 8255 sont numerotees 4,3,2,1 puis
// 40,39,38,37 pour PA0..PA7). Si vous recablez A3->PA7 ... A0->PA4, remettez
// {10, 11, 12, 13, A0, A1, A2, A3}.
const uint8_t BUS[8]       = {10, 11, 12, 13, A3, A2, A1, A0};

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
// Arduino -> 8088: octet + etiquette, puis impulsion STB#.
static void sendTo8088(uint8_t tag, uint8_t v) {
  digitalWrite(PIN_TAG, tag);
  for (uint8_t i = 0; i < 8; i++) {
    digitalWrite(BUS[i], (v >> i) & 1);    // niveau AVANT de passer en sortie
    pinMode(BUS[i], OUTPUT);
  }
  delayMicroseconds(2);
  digitalWrite(PIN_STB, LOW);
  delayMicroseconds(2);
  digitalWrite(PIN_STB, HIGH);             // front montant: le 8255 verrouille
  delayMicroseconds(2);
  busRelease();
}
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// pilote le bus; les broches sont des entrees a ce moment-la. Le canal (Port
// B) est stable depuis que le 8088 a ecrit le Port A - meme instantane.
static bool takeFrom8088(uint8_t &chan, uint8_t &val) {
  if (digitalRead(PIN_OBF)) return false;  // rien en attente
  digitalWrite(PIN_ACK, LOW);
  delayMicroseconds(2);                    // tAOD du 8255 < 200 ns
  uint32_t s = snapPorts();
  digitalWrite(PIN_ACK, HIGH);
  chan = (uint8_t)(snapBit(s, PIN_CH0) | (snapBit(s, PIN_CH1) << 1));
  val = 0;
  for (uint8_t i = 0; i < 8; i++) val |= (uint8_t)(snapBit(s, BUS[i]) << i);
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  uint32_t now = micros();
  ps2Act = now;
  delayMicroseconds(PS2_GLITCH_US);
  if (PIND & _BV(PIN_PS2_CLK)) { dbg(0x700); return; }   // CLK repassee haute: parasite

  // DATA: vote majoritaire sur 3 lectures (encore stable a ce stade du cycle)
  uint8_t votes = 0;
  if (PIND & _BV(PIN_PS2_DATA)) votes++;
  delayMicroseconds(2);
  if (PIND & _BV(PIN_PS2_DATA)) votes++;
  delayMicroseconds(2);
  if (PIND & _BV(PIN_PS2_DATA)) votes++;
  uint8_t b = (votes >= 2) ? 1 : 0;

  if ((uint32_t)(now - ps2Last) > PS2_FRAME_GAP_US) {   // nouvelle trame
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
// ============================================================================
void setup() {
  pinMode(PIN_ACK, OUTPUT);  digitalWrite(PIN_ACK, HIGH);
  pinMode(PIN_STB, OUTPUT);  digitalWrite(PIN_STB, HIGH);
  pinMode(PIN_TAG, OUTPUT);  digitalWrite(PIN_TAG, LOW);
  pinMode(PIN_OBF, INPUT_PULLUP);          // 8255 absent/hors tension = "rien"
  pinMode(PIN_CH0, INPUT);
  pinMode(PIN_CH1, INPUT);
  busRelease();
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#endif
  lcdInit();

  pinMode(PIN_PS2_CLK, INPUT_PULLUP);
  pinMode(PIN_PS2_DATA, INPUT_PULLUP);
  attachInterrupt(digitalPinToInterrupt(PIN_PS2_CLK), ps2Isr, FALLING);
}

void loop() {
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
